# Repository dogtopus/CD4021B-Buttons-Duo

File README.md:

# CD4021B-Buttons-Duo

16 channel arcade button driver

(Legacy project, no longer in development)

## Features

- 16 channels
  - 8 channels for regular (NC and/or NO, depends on the software) buttons
  - 8 channels for illuminated (lamp equipped) buttons
- Programmable lamps
- Button interface are somewhat compatible with [CY-822B][1] encoder (shares
  the same electrical interface) with a better (not hard-wired to VBUS) lamp
  support.
- Separated lamp power rail (Supports 0-12V PSU, 500mA max for each channel)
- Supports 3.3V (at low speed like 1-2MHz) and 5V logic
- Supports controlling via SPI bus and bitbang with Arduino ShiftIn/ShiftOut
  code

## Usage

- Install KiCad
- Plot the board
- Zip the Gerber files and send them to whatever PCB house you like
- TODO components, BOM, etc.
- ???
- PROFIT!

PS: There's no plan for selling the assembled boards or kits at the moment,
so too bad for those who just want a working board :<

## Notes

- First and foremost, I am still very new to PCB layout and routing, so feel
  free to open an issue to give suggestions on my design and/or point out any
  mistakes I made.
- The JST connectors are rotated 180 degrees (so pin 1 is on the **right**
  side) due to a mistake I made at the very early stage of designing and the
  quickest way of fixing it is to rotate the connector.
- Make sure you are using the **"always on"** wiring suggested [here][1] (i.e.
  pin 1 is common ground, pin 2 is button and pin 3 is lamp)
  for illuminated buttons. Behavior on "illuminate on press" wiring (i.e.
  reversing pin 1 and pin 2) is undefined
  (and potentially dangerous if the lamps are powered with voltage higher or
  lower than VCC since this wiring basically shorts the lamp power to the button
  pin when the switch on the button is closed)
- The P-channel MOSFET can be swapped for cheaper alternative (e.g. CJL3415) as
  long as they have the same electrical interface, 
  the parameters (Vds, Vgs, Ids, Rds) are reasonable and proper zener diodes
  (D1-D8) and voltage divider (R1-R8, R9-R16) are chosen so that the gate of the
  MOSFET are not overdriven. (In case of CJL3415, a good choice would be 10k for
  R9-R16, 20k for R1-R8, and zeners with zener voltage of 7.5V)
  Also, TPIC6C596 can be used in place of TPIC6C595. (Tested)

[1]: https://cy-822b.blogspot.com/2016/08/the-cy-822b-usb-led-joystick-controller.html

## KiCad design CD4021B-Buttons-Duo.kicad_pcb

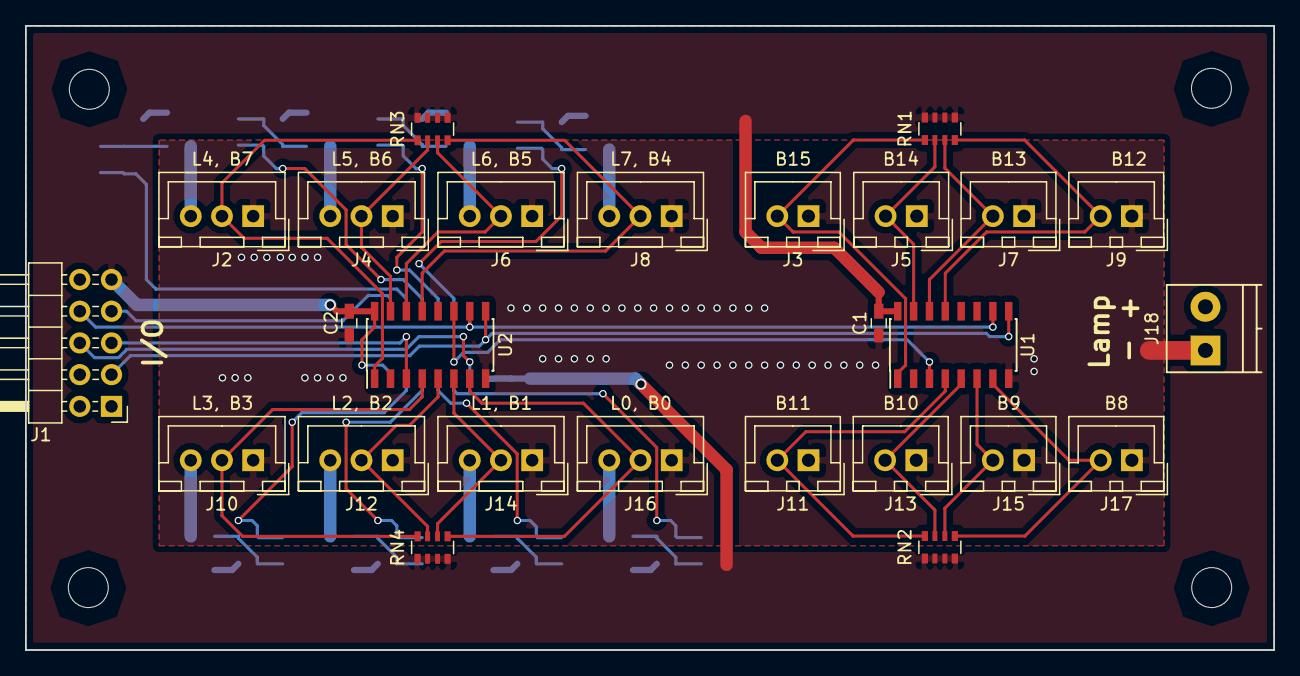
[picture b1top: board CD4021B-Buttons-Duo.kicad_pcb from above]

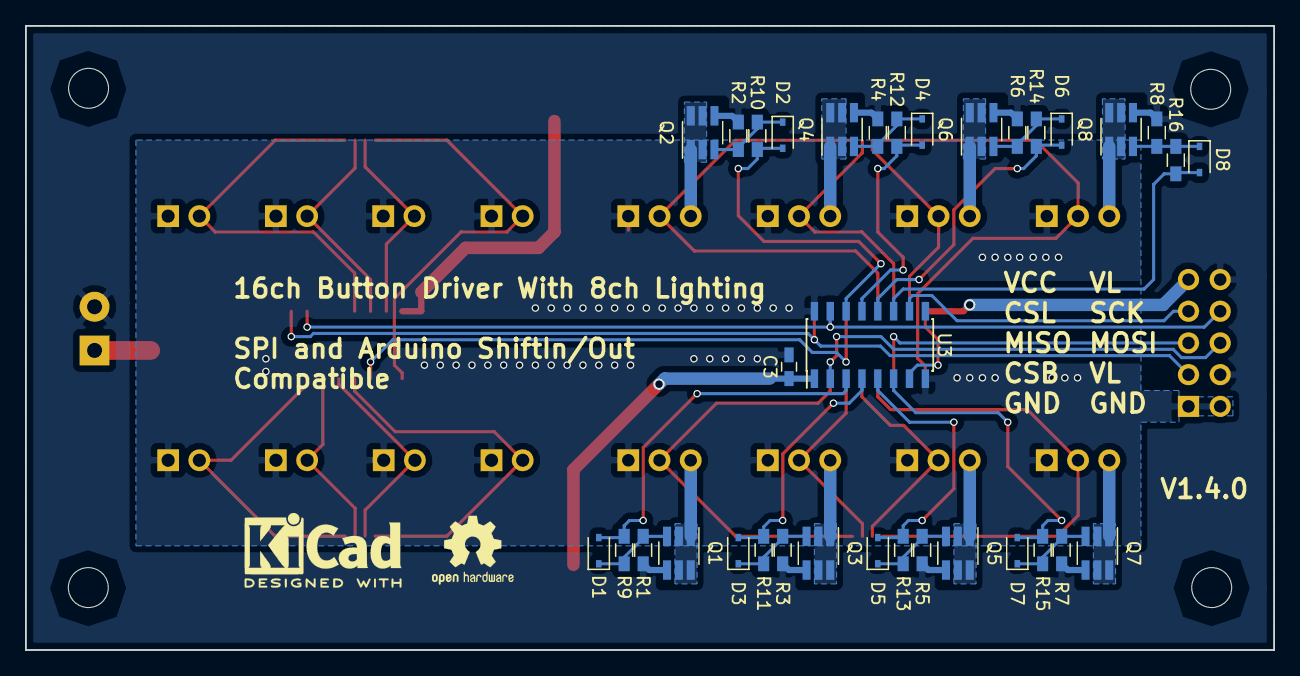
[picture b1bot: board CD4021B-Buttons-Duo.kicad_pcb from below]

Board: 2 copper layers, 100.0 x 50.0 mm, 60 parts (34 on the bottom side), 49 nets.

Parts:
C1, C2, C3: 100nF; C_0603_HandSoldering
D1, D2, D3, D4, D5, D6, D7, D8: Zener; D_SOD-323
J1: 2.54; Pin_Header_Angled_2x05_Pitch2.54mm
J2, J4, J6, J8, J10, J12, J14, J16: JST XH; JST_XH_B03B-XH-A_03x2.50mm_Straight
J3, J5, J7, J9, J11, J13, J15, J17: JST XH; JST_XH_B02B-XH-A_02x2.50mm_Straight
J18: 3.5; TerminalBlock_Phoenix_PT-3.5mm_2pol
Q1, Q2, Q3, Q4, Q5, Q6, Q7, Q8: IRF5806; SOT-23-6_Handsoldering
R1, R2, R3, R4, R5, R6, R7, R8: 10k; R_0603_HandSoldering
R9, R10, R11, R12, R13, R14, R15, R16: 0; R_0603_HandSoldering
RN1, RN2, RN3, RN4: 10k x4; R_Array_Convex_4x0603
U1, U2: CD4021BM; SOIC-16_3.9x9.9mm_Pitch1.27mm
U3: TPIC6C595D; SOIC-16_3.9x9.9mm_Pitch1.27mm

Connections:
+12V: J1.4, J1.10, J18.2, Q1.4, Q2.4, Q3.4, Q4.4, Q5.4, Q6.4, Q7.4, Q8.4, R1.2, R2.2, R3.2, R4.2, R5.2, R6.2, R7.2, R8.2
/CHAIN: U1.3, U2.11
/CSI: J1.3, U1.9, U2.9
/CSO: J1.7, U3.10
/D0: J16.2, RN4.5, U2.7
/D1: J14.2, RN4.6, U2.6
/D2: J12.2, RN4.7, U2.5
/D3: J10.2, RN4.8, U2.4
/D4: J8.2, RN3.4, U2.13
/D5: J6.2, RN3.3, U2.14
/D6: J4.2, RN3.2, U2.15
/D7: J2.2, RN3.1, U2.1
/D8: J17.2, RN2.5, U1.7
/D9: J15.2, RN2.6, U1.6
/D10: J13.2, RN2.7, U1.5
/D11: J11.2, RN2.8, U1.4
/D12: J9.2, RN1.4, U1.13
/D13: J7.2, RN1.3, U1.14
/D14: J5.2, RN1.2, U1.15
/D15: J3.2, RN1.1, U1.1
/L0: J16.3, Q1.1, Q1.2, Q1.5, Q1.6
/L1: J14.3, Q3.1, Q3.2, Q3.5, Q3.6
/L2: J12.3, Q5.1, Q5.2, Q5.5, Q5.6
/L3: J10.3, Q7.1, Q7.2, Q7.5, Q7.6
/L4: J8.3, Q2.1, Q2.2, Q2.5, Q2.6
/L5: J6.3, Q4.1, Q4.2, Q4.5, Q4.6
/L6: J4.3, Q6.1, Q6.2, Q6.5, Q6.6
/L7: J2.3, Q8.1, Q8.2, Q8.5, Q8.6
/LD0: D1.2, R9.1, U3.3
/LD1: D3.2, R11.1, U3.4
/LD2: D5.2, R13.1, U3.5
/LD3: D7.2, R15.1, U3.6
/LD4: D2.2, R10.1, U3.14
/LD5: D4.2, R12.1, U3.13
/LD6: D6.2, R14.1, U3.12
/LD7: D8.2, R16.1, U3.11
/MISO: J1.5, U2.3
/MOSI: J1.6, U3.2
/SCK: J1.8, U1.10, U2.10, U3.15
GND: C1.2, C2.2, C3.2, J1.1, J1.2, J2.1, J3.1, J4.1, J5.1, J6.1, J7.1, J8.1, J9.1, J10.1, J11.1, J12.1, J13.1, J14.1, J15.1, J16.1, J17.1, J18.1, U1.8, U2.8, U3.8, U3.16
unnamed: D1.1, Q1.3, R1.1, R9.2
unnamed: D2.1, Q2.3, R2.1, R10.2
unnamed: D3.1, Q3.3, R3.1, R11.2
unnamed: D4.1, Q4.3, R4.1, R12.2
unnamed: D5.1, Q5.3, R5.1, R13.2
unnamed: D6.1, Q6.3, R6.1, R14.2
unnamed: D7.1, Q7.3, R7.1, R15.2
unnamed: D8.1, Q8.3, R8.1, R16.2
VCC: C1.1, C2.1, C3.1, J1.9, RN1.5, RN1.6, RN1.7, RN1.8, RN2.1, RN2.2, RN2.3, RN2.4, RN3.5, RN3.6, RN3.7, RN3.8, RN4.1, RN4.2, RN4.3, RN4.4, U1.16, U2.16, U3.1, U3.7

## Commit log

2018-05-15 README
2018-05-16 Register a generic name for IRF5806
2018-05-16 Re-place some via stitches so that they are not under silkscreens
2018-05-16 Enable the NC pin as an alternate lamp power pin to (hopefully) allow more current
2018-05-16 Change the pinout silkscreen
2018-05-16 Add open source hardware logo because why not
2018-05-22 Enlarge grond plane, adjust logo positioning
2018-05-23 Cleanup via stitches
2018-05-23 Change the board dimension to be exactly 100x50mm
2018-05-23 Move logo (again)
2018-05-23 Independent power connector for lamp power
2018-05-23 Add screw terminal to the board for lamp power
2018-05-23 Re-routed using vertical-horizontal routing rule
2018-05-23 Minor adjustment
2018-05-23 Minor cleanup
2018-05-23 Attempt to optimize connections for bypass capacitors
2018-05-23 Cosmetic
2018-05-25 Adjust traces
2018-05-26 Use thinner traces for local VCC connections
2018-05-26 Move VCC trace for U1
2018-05-26 Attempt to reduce via usage on LD* traces
2018-05-29 License for documents
2018-05-29 Not needed anymore
2018-05-29 Add a demo program for Arduino
2018-05-30 Update component metadata
2018-05-30 Include missing metadata file
2018-05-30 Add a note about the MOSFET and TPIC6C595
2018-05-30 Add a 0ohm jumper between PMOS gate and DRAIN* pin
2018-05-30 Map footprint
2018-05-31 Add zener on PMOS gates for extra assurance
2018-06-11 Switch the pad connection of VCC planes back to thermal relief
2018-06-11 Add voltage divider to the PMOS gate on the board
2018-06-11 Update notice about PMOS in README
2018-06-11 The anode of the zener should be connected to the DRAIN* pin instead of GND
    Otherwise the MOSFET always conducts
2018-06-18 Cleanup: Make LD7 completely on the back side
2018-06-18 Add more info on lamp PMOS alternative
2018-07-24 Change CSI/CSO to CSB (button)/CSL (lamp) to avoid confusion
2018-07-24 Derp
2018-08-03 Clarify
2018-08-03 Set aux axis origin to the top left corner of the board
2018-08-03 Update labelling for CSL and CSB pins
2018-09-16 Fix symbol problem, again.
2019-05-13 Mark as legacy #RIP
